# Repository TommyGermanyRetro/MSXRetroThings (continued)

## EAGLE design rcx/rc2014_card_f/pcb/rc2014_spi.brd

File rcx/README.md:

# RCX ROM cartridge - command reference

The RCX ROM cartridge manages up to 16 RC2014 cards. Its ROM (or the RAM driver `RCXRAM.COM`) adds BASIC `CALL` commands and an UNAPI/EXTBIOS interface; the SDCC library `rcx_io` bridges to the same functions. This page lists the general RCX commands; the commands of each card are on the card's page.

## Cards

+ [A) RC2014 card with PCF8584 I2C Controller (3 ports via Seeed) and PCF8583 battery buffered RTC](rc2014_card_a/README.md)
+ [B) RC2014 card SC103 with Z80 PIO](rc2014_card_b/README.md)
+ [C) RC2014 card with 8255A PIO](rc2014_card_c/README.md)
+ [D) RC2014 card with 8254A CTR](rc2014_card_d/README.md)
+ [E) RC2014 card with SJA1000 CAN controller (single use only)](rc2014_card_e/README.md)
+ [F) RC2014 card with 4x SPI bus up to 2 MHz via ATMEGA8](rc2014_card_f/README.md)
+ [G) RC2014 card with ADS1220 4 channel 24 bit A/D converter via ATMEGA8](rc2014_card_g/README.md)
+ [H) RC2014 card SC725 with Z80 SIO and Z80 CTC](rc2014_card_h/README.md)
+ [I) RC2014 card with MCP4822 4 channel 12 bit D/A converter via ATMEGA8](rc2014_card_i/README.md)

## Command reference

Commands implemented in ROM/DRV/LIB for steering and controlling of the cards functions:

+ <i><b>RCX ?</i></b>

  Prints the list of available RCX commands directly to the screen. Works independently from RCX INIT, so it is always safe to call even if no card has been registered yet.

|  | Definition | BASIC* | UNAPI | SDCC |
| --- | --- | --- | --- | --- |
| Syntax | RCX ? | _RCX ? | 1 | - (BASIC-only, not exposed) |

*) ROM only

+ <i><b>RCX INIT</i></b>

  Installs the RCX driver itself: allocates and clears the internal table that tracks which RC2014 card types are registered at which IO address. Every other RCX/card-specific command needs this table to exist, so it must run before any card-type INIT (I2C INIT, PIO INIT, etc.); calling it again while already installed just resets the table.

|  | Definition | BASIC* | UNAPI | SDCC |
| --- | --- | --- | --- | --- |
| Syntax | RCX INIT | _RCX INIT | 2 | Rcx_Init() |
| PARA 1 | Working area in RAM | automatic by BIOS | HL | word |

*) ROM only

+ <i><b>RCX ISINIT</i></b>

  Checks whether the RCX driver is already installed, without touching anything - same ISINIT/DEINIT/INIT pattern as XIO ISINIT.

|  | Definition | BASIC* | UNAPI | SDCC |
| --- | --- | --- | --- | --- |
| Syntax | RCX ISINIT | _RCX ISINIT() | 3 | Rcx_IsInit() |
| PARA 1 | 0 = not installed, 1 = installed | variable | DE as varptr | return value (byte) |

*) ROM only

+ <i><b>RCX DEINIT</i></b>

  Uninstalls the RCX driver and frees the card table again.

|  | Definition | BASIC* | UNAPI | SDCC |
| --- | --- | --- | --- | --- |
| Syntax | RCX DEINIT | _RCX DEINIT | 4 | Rcx_Deinit() |

*) ROM only

+ <i><b>RCX TABLE</i></b>

  Returns the RAM address of the internal per-slot card table directly, mainly useful for diagnostics - inspecting which addresses and card types are currently registered without a dedicated command for each one.

|  | Definition | BASIC* | UNAPI | SDCC |
| --- | --- | --- | --- | --- |
| Syntax | RCX TABLE | _RCX TABLE() | 5 | Rcx_GetTable() |
| PARA 1 | ADDR of RCX table | variable | DE as varptr | pointer (word) |

*) ROM only

## Folders

+ [rc2014_rom+ram/rom/](rc2014_rom+ram/rom/README.md) - ROM source and image
+ [rc2014_rom+ram/drv/](rc2014_rom+ram/drv/README.md) - RAM driver `RCXRAM.COM`
+ [rc2014_rom+ram/pcb/](rc2014_rom+ram/pcb/) - schematics and PCB of the ROM cartridge
+ [rc2014_adapter/pcb/](rc2014_adapter/pcb/) - schematics and PCB of the RC2014 adapter
+ [rcxslt/](rcxslt/) - RCX slot tools (BASIC, `.COM`, SDCC)

[↑ Main README](../README.md#2-msxretrothings---the-rcx-rom-cartridge-and-rc2014-cards)

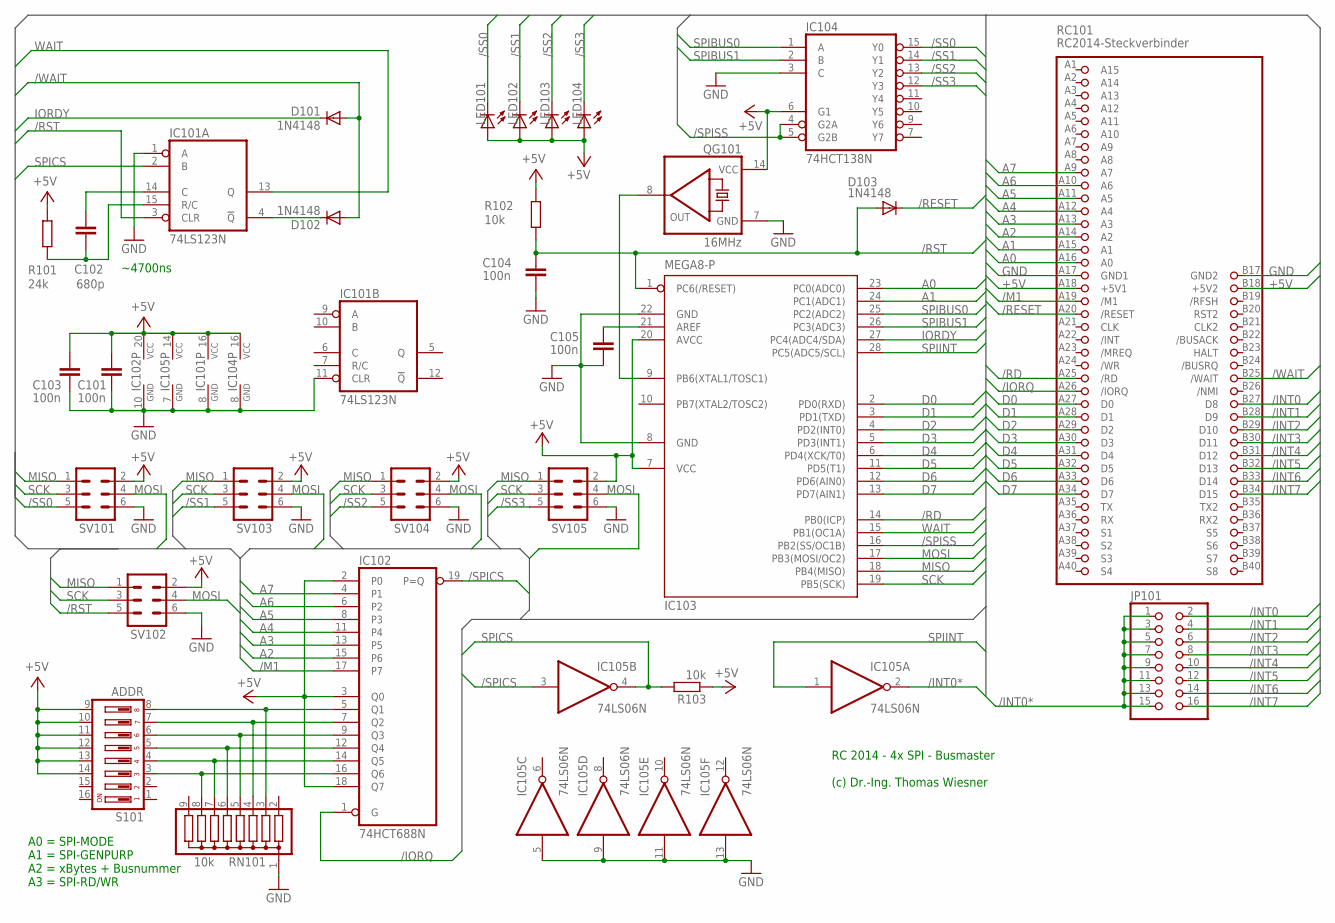
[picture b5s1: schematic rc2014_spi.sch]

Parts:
C101, C103, C104, C105: 100n; C025-025X050
C102: 680p; C025-025X050
D101, D102, D103: 1N4148; DO35-10
IC101: 74LS123N; DIL16
IC102: 74HCT688N; DIL20
IC103: MEGA8-P; DIL28-3
IC104: 74HCT138N; DIL16
IC105: 74LS06N; DIL14
JP101: PINHD-2X8; 2X08
LED101, LED102, LED103, LED104: LED3MM
QG101: 16MHz; DIL14S
R101: 24k; 0207/10
R102, R103: 10k; 0207/10
RC101: RC2014-Steckverbinder; RC2014-STECKER
RN101: 10k; SIL9
S101: ADDR; DS-08
SV101, SV102, SV103, SV104, SV105: ML6L

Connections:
+5V: C101.2, C103.2, IC101.16 (VCC), IC102.2 (P0), IC102.3 (Q0), IC102.18 (Q7), IC102.20 (VCC), IC103.7 (VCC), IC103.20 (AVCC), IC104.6 (G1), IC104.16 (VCC), IC105.14 (VCC), LED101.A, LED102.A, LED103.A, LED104.A, QG101.14 (VCC), R101.1, R102.1, R103.1, RC101.A18 (+5V1), RC101.B18 (+5V2), S101.9, S101.10, S101.11, S101.12, S101.13, S101.14, SV101.2, SV102.2, SV103.2, SV104.2, SV105.2
/INT0: JP101.2, RC101.B27 (D8)
/INT0*: IC105.2 (O), JP101.1, JP101.3, JP101.5, JP101.7, JP101.9, JP101.11, JP101.13, JP101.15
/INT1: JP101.4, RC101.B28 (D9)
/INT2: JP101.6, RC101.B29 (D10)
/INT3: JP101.8, RC101.B30 (D11)
/INT4: JP101.10, RC101.B31 (D12)
/INT5: JP101.12, RC101.B32 (D13)
/INT6: JP101.14, RC101.B33 (D14)
/INT7: JP101.16, RC101.B34 (D15)
/IORQ: IC102.1 (G), RC101.A26 (/IORQ)
/M1: IC102.17 (P7), RC101.A19 (/M1)
/RD: IC103.14 (PB0(ICP)), RC101.A25 (/RD)
/RESET: D103.C, RC101.A20 (/RESET)
/RST: C104.2, D103.A, IC101.3 (CLR), IC103.1 (PC6(/RESET)), R102.2, SV102.5
/SPICS: IC102.19 (P=Q), IC105.3 (I)
/SPISS: IC103.16 (PB2(SS/OC1B)), IC104.4 (G2A), IC104.5 (G2B)
/SS0: IC104.15 (Y0), LED101.K (C), SV101.5
/SS1: IC104.14 (Y1), LED102.K (C), SV103.5
/SS2: IC104.13 (Y2), LED103.K (C), SV104.5
/SS3: IC104.12 (Y3), LED104.K (C), SV105.5
/WAIT: D101.A, D102.A, RC101.B25 (/WAIT)
A0: IC103.23 (PC0(ADC0)), RC101.A16 (A0)
A1: IC103.24 (PC1(ADC1)), RC101.A15 (A1)
A2: IC102.15 (P6), RC101.A14 (A2)
A3: IC102.13 (P5), RC101.A13 (A3)
A4: IC102.11 (P4), RC101.A12 (A4)
A5: IC102.8 (P3), RC101.A11 (A5)
A6: IC102.6 (P2), RC101.A10 (A6)
A7: IC102.4 (P1), RC101.A9 (A7)
D0: IC103.2 (PD0(RXD)), RC101.A27 (D0)
D1: IC103.3 (PD1(TXD)), RC101.A28 (D1)
D2: IC103.4 (PD2(INT0)), RC101.A29 (D2)
D3: IC103.5 (PD3(INT1)), RC101.A30 (D3)
D4: IC103.6 (PD4(XCK/T0)), RC101.A31 (D4)
D5: IC103.11 (PD5(T1)), RC101.A32 (D5)
D6: IC103.12 (PD6(AIN0)), RC101.A33 (D6)
D7: IC103.13 (PD7(AIN1)), RC101.A34 (D7)
GND: C101.1, C103.1, C104.1, C105.1, IC101.1 (A), IC101.8 (GND), IC101.11 (CLR), IC102.10 (GND), IC103.8 (GND), IC103.22 (GND), IC104.3 (C), IC104.8 (GND), IC105.5 (I), IC105.7 (GND), IC105.9 (I), IC105.11 (I), IC105.13 (I), QG101.7 (GND), RC101.A17 (GND1), RC101.B17 (GND2), RN101.1, SV101.6, SV102.6, SV103.6, SV104.6, SV105.6
IORDY: D101.C, IC103.27 (PC4(ADC4/SDA))
MISO: IC103.18 (PB4(MISO)), SV101.1, SV102.1, SV103.1, SV104.1, SV105.1
MOSI: IC103.17 (PB3(MOSI/OC2)), SV101.4, SV102.4, SV103.4, SV104.4, SV105.4
unnamed: C102.1, IC101.15 (R/C), R101.2
unnamed: D102.C, IC101.4 (!Q)
unnamed: C105.2, IC103.21 (AREF)
unnamed: C102.2, IC101.14 (C)
unnamed: IC102.16 (Q6), RN101.8, S101.3
unnamed: IC102.14 (Q5), RN101.7, S101.4
unnamed: IC102.12 (Q4), RN101.6, S101.5
unnamed: IC102.9 (Q3), RN101.5, S101.6
unnamed: IC102.7 (Q2), RN101.4, S101.7
unnamed: IC102.5 (Q1), RN101.3, S101.8
QUARZ: IC103.9 (PB6(XTAL1/TOSC1)), QG101.8 (OUT)
SCK: IC103.19 (PB5(SCK)), SV101.3, SV102.3, SV103.3, SV104.3, SV105.3
SPIBUS0: IC103.25 (PC2(ADC2)), IC104.1 (A)
SPIBUS1: IC103.26 (PC3(ADC3)), IC104.2 (B)
SPICS: IC101.2 (B), IC105.4 (O), R103.2
SPIINT: IC103.28 (PC5(ADC5/SCL)), IC105.1 (I)
WAIT: IC101.13 (Q), IC103.15 (PB1(OC1A))

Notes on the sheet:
RC 2014 - 4x SPI - Busmaster (c) Dr.-Ing. Thomas Wiesner
~4700ns
A0 = SPI-MODE A1 = SPI-GENPURP A2 = xBytes + Busnummer A3 = SPI-RD/WR

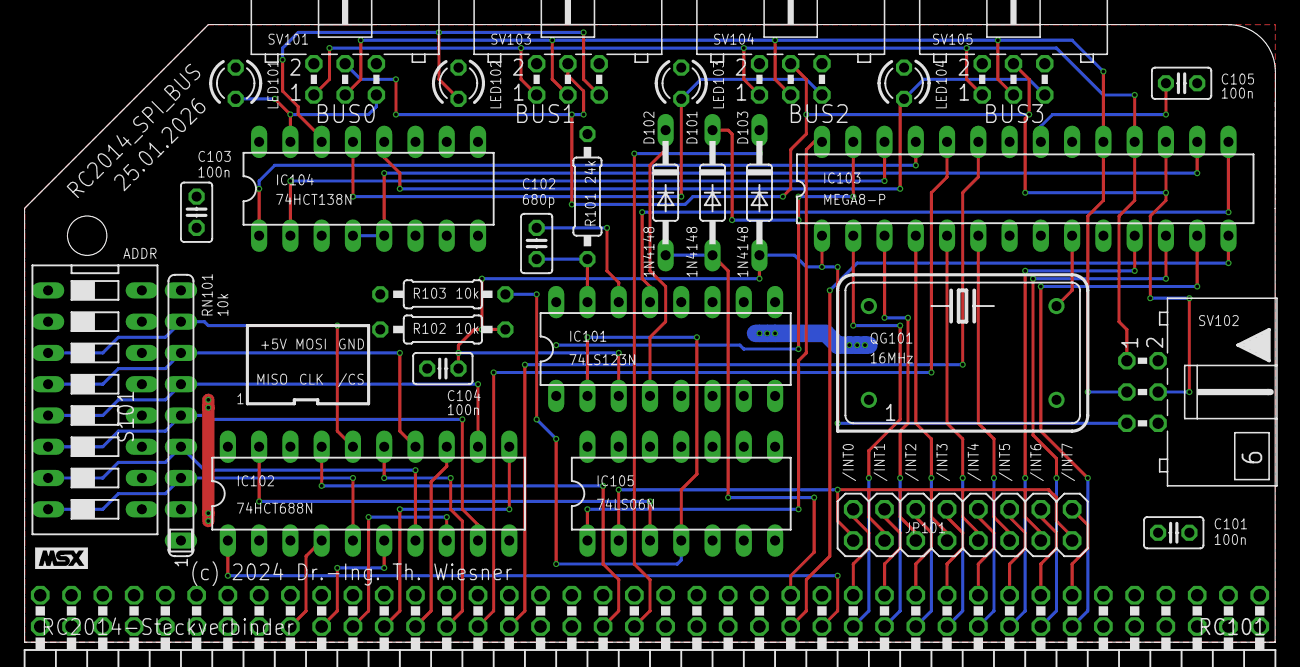
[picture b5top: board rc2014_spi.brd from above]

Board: 2 copper layers, 101.6 x 50.2 mm, 30 parts (0 on the bottom side), 59 nets.

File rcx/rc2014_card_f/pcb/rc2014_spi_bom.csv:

Qty,Reference,Value,Package,Description
1,RC101,RC2014,RC2014-STECKER,"RC2014 enhanced bus connector, pin header 2 x 40, 2.54 mm, angled"
1,IC103,ATmega8,DIL28-3,"Microcontroller ATmega8, flashed with atmel/MSXSPI/MSXSPI.ino"
1,IC102,74HCT688N,DIL20,8-bit comparator: card address against the DIP switch
1,IC104,74HCT138N,DIL16,3-to-8 decoder: SPI slave select /SS0-/SS3
1,IC101,74LS123N,DIL16,Dual monostable multivibrator
1,IC105,74LS06N,DIL14,"Hex inverter, open collector"
1,QG101,16MHz,DIL14S,"Crystal oscillator 16 MHz, DIL14 footprint"
4,"C101, C103, C104, C105",100n,C025-025X050,"Ceramic capacitor 100 nF, 2.5 mm pitch"
1,C102,680p,C025-025X050,"Ceramic capacitor 680 pF, 2.5 mm pitch"
3,"D101, D102, D103",1N4148,DO35-10,Signal diode
1,R101,24k,0207/10,"Resistor 24 kOhm, axial, 10 mm pitch"
2,"R102, R103",10k,0207/10,"Resistor 10 kOhm, axial, 10 mm pitch"
1,RN101,10k,SIL9,"Resistor network 8 x 10 kOhm, common pin, SIL9"
1,S101,ADDR,DS-08,DIP switch 8 positions: card address
4,"LED101, LED102, LED103, LED104",LED,LED3MM,LED 3 mm with built-in resistor for 5 V: SPI slave select /SS0-/SS3 active
4,"SV101, SV103, SV104, SV105",Box header 2x3,ML6L,"Box header 6 pins (2 x 3), 2.54 mm: SPI ports 0-3 (MISO, SCK, MOSI, /SS, +5 V, GND)"
1,SV102,Box header 2x3,ML6L,"Box header 6 pins (2 x 3), 2.54 mm: ISP connector of the ATmega8"
1,JP101,2X08,2X08,"Pin header 2 x 8, 2.54 mm, with jumper: selects the interrupt line /INT0-/INT7 of the XIO PIC"

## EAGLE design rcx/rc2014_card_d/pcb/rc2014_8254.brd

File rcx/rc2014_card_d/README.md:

# Card D - RC2014 card with 8254A CTR

RC2014 card with a 8254 CTR. Up to 16 cards are possible. The interrupt pins of TIMER 0 and 1 can be assigned to one of the XIO PIC interrupt channels. This module does not work with internal clock if 8253 (max. 1 MHz) is used.

## Command reference

Commands implemented in ROM:

+ <i><b>TIMER INIT</i></b>

  Registers the card's IO base address in the RCX table. Must be called once per card before any of the other TIMER commands below will find it.

|  | Definition | BASIC* | UNAPI | SDCC |
| --- | --- | --- | --- | --- |
| Syntax | TIMER INIT | _TIMER INIT() | 33 | Timer_Init() |
| PARA 1 | IO addr 0...251 | byte or variable | C | byte or variable |

*) ROM only

+ <i><b>TIMER 0 RD</i></b>

  Latches and reads the current 16-bit counter value of Timer 0.

|  | Definition | BASIC* | UNAPI | SDCC |
| --- | --- | --- | --- | --- |
| Syntax | TIMER 0 RD | _TIMER 0 RD() | 34 | Timer_Read0() |
| PARA 1 | IO addr 0...251 | byte or variable | C | byte or variable |
| PARA 2 | Word to read | variable | DE as varptr | return value (word) |
| PARA 3 | UNAPI ID Level 2 | -/- | B = 0 | - |

*) ROM only

+ <i><b>TIMER 0 WR</i></b>

  Loads a new 16-bit count/reload value into Timer 0.

|  | Definition | BASIC* | UNAPI | SDCC |
| --- | --- | --- | --- | --- |
| Syntax | TIMER 0 WR | _TIMER 0 WR() | 35 | Timer_Write0() |
| PARA 1 | IO addr 0...251 | byte or variable | C | byte or variable |
| PARA 2 | Word to write | word or variable | DE | word or variable |
| PARA 3 | UNAPI ID Level 2 | -/- | B = 1 | - |

*) ROM only

+ <i><b>TIMER 1 RD</i></b>

  Latches and reads the current 16-bit counter value of Timer 1.

|  | Definition | BASIC* | UNAPI | SDCC |
| --- | --- | --- | --- | --- |
| Syntax | TIMER 1 RD | _TIMER 1 RD() | 36 | Timer_Read1() |
| PARA 1 | IO addr 0...251 | byte or variable | C | byte or variable |
| PARA 2 | Word to read | variable | DE as varptr | return value (word) |
| PARA 3 | UNAPI ID Level 2 | -/- | B = 2 | - |

*) ROM only

+ <i><b>TIMER 1 WR</i></b>

  Loads a new 16-bit count/reload value into Timer 1.

|  | Definition | BASIC* | UNAPI | SDCC |
| --- | --- | --- | --- | --- |
| Syntax | TIMER 1 WR | _TIMER 1 WR() | 37 | Timer_Write1() |
| PARA 1 | IO addr 0...251 | byte or variable | C | byte or variable |
| PARA 2 | Word to write | word or variable | DE | word or variable |
| PARA 3 | UNAPI ID Level 2 | -/- | B = 3 | - |

*) ROM only

+ <i><b>TIMER 2 RD</i></b>

  Latches and reads the current 16-bit counter value of Timer 2.

|  | Definition | BASIC* | UNAPI | SDCC |
| --- | --- | --- | --- | --- |
| Syntax | TIMER 2 RD | _TIMER 2 RD() | 38 | Timer_Read2() |
| PARA 1 | IO addr 0...251 | byte or variable | C | byte or variable |
| PARA 2 | Word to read | variable | DE as varptr | return value (word) |
| PARA 3 | UNAPI ID Level 2 | -/- | B = 4 | - |

*) ROM only

+ <i><b>TIMER 2 WR</i></b>

  Loads a new 16-bit count/reload value into Timer 2.

|  | Definition | BASIC* | UNAPI | SDCC |
| --- | --- | --- | --- | --- |
| Syntax | TIMER 2 WR | _TIMER 2 WR() | 39 | Timer_Write2() |
| PARA 1 | IO addr 0...251 | byte or variable | C | byte or variable |
| PARA 2 | Word to write | word or variable | DE | word or variable |
| PARA 3 | UNAPI ID Level 2 | -/- | B = 5 | - |

*) ROM only

+ <i><b>TIMER CTRL</i></b>

  Writes the 82C54's mode-control word for one of the three counters - selects counting mode 0..5, BCD vs. binary counting and the read/write byte order, matching the 82C54 datasheet's control word format directly.

|  | Definition | BASIC* | UNAPI | SDCC |
| --- | --- | --- | --- | --- |
| Syntax | TIMER CTRL | _TIMER CTRL() | 40 | Timer_Ctrl() |
| PARA 1 | IO addr 0...251 | byte or variable | C | byte or variable |
| PARA 2 | Word to write | word or variable | E (D must be 0) | word or variable |
| PARA 3 | UNAPI ID Level 2 | -/- | B = 6 | - |

*) ROM only

+ <i><b>TIMER SET GATE</i></b>

  Drives one of the card's jumper-selectable GATE inputs high in software instead of wiring it permanently - only takes effect for a counter whose GATE jumper is actually set to the software-controlled position.

	Value 0..7 is allowed

|  | Definition | BASIC* | UNAPI | SDCC |
| --- | --- | --- | --- | --- |
| Syntax | TIMER SET GATE | _TIMER SET GATE() | 41 | Timer_SetGate() |
| PARA 1 | IO addr 0...251 | byte or variable | C | byte or variable |
| PARA 2 | GATE 0..3 (0..7) | byte or variable | E (D must be 0) | word or variable |
| PARA 3 | UNAPI ID Level 2 | -/- | B = 7 | - |

*) ROM only

+ <i><b>TIMER RESET GATE</i></b>

  Drives a jumper-selectable GATE input low again - the counterpart to TIMER SET GATE.

	Value 0..7 is allowed

|  | Definition | BASIC* | UNAPI | SDCC |
| --- | --- | --- | --- | --- |
| Syntax | TIMER RESET GATE | _TIMER RESET GATE() | 42 | Timer_ResetGate() |
| PARA 1 | IO addr 0...251 | byte or variable | C | byte or variable |
| PARA 2 | GATE 0..3 (0..7) | byte or variable | E (D must be 0) | word or variable |
| PARA 3 | UNAPI ID Level 2 | -/- | B = 8 | - |

*) ROM only

## Folders

+ [basic/](basic/README.md) - BASIC test programs
+ [com/](com/README.md) - `.COM` tools (UNAPI/EXTBIOS)
+ [sdcc/](sdcc/README.md) - SDCC tools
+ [pcb/](pcb/) - schematics, PCB, Gerber and drill files, bill of materials

[↑ Main README](../../README.md#d-rc2014-card-with-8254a-ctr)

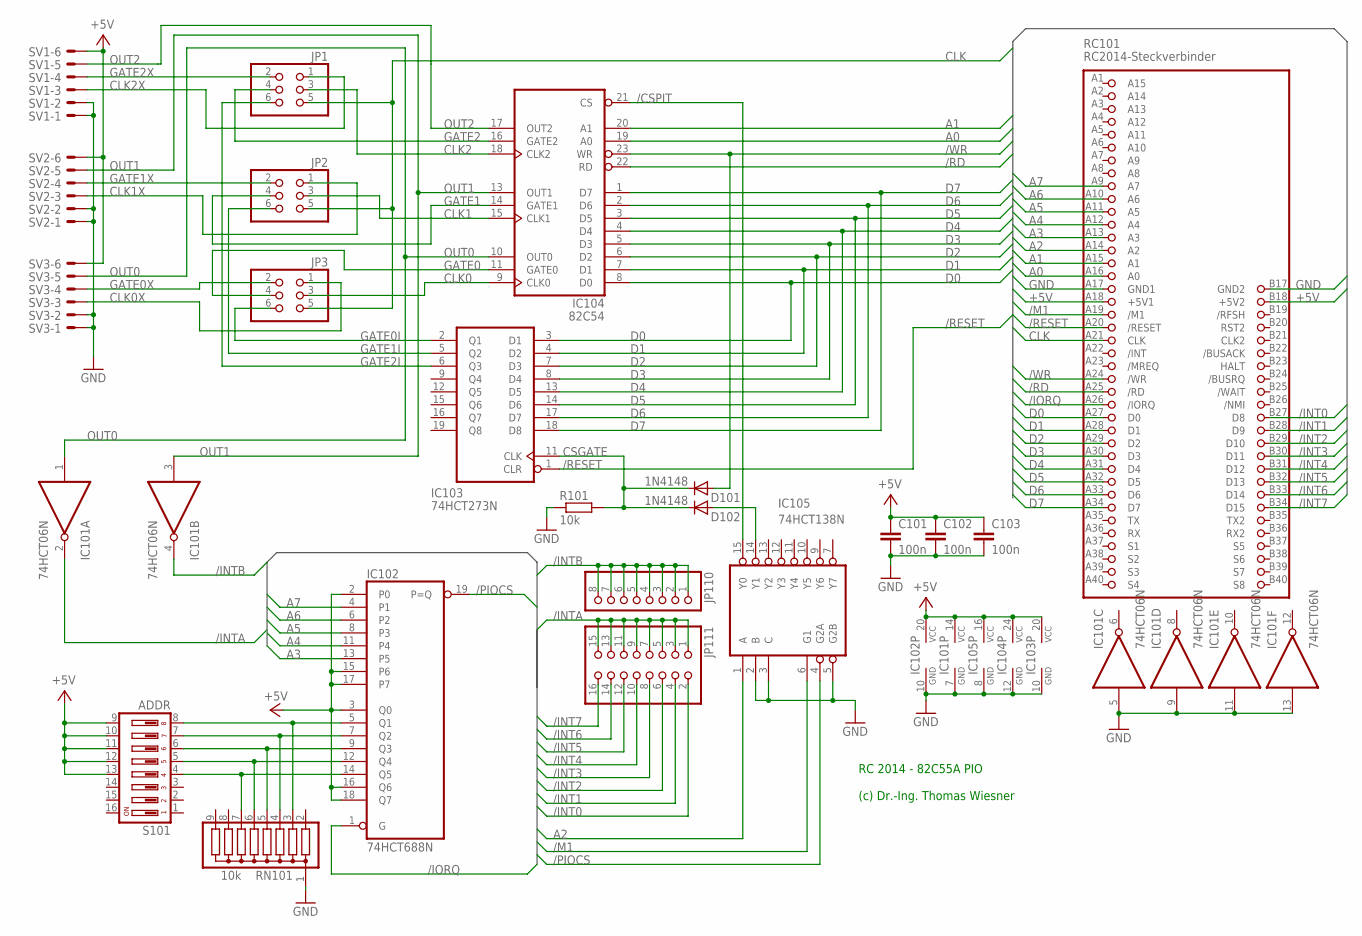
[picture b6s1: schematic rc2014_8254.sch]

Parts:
C101, C102, C103: 100n; C025-025X050
D101, D102: 1N4148; DO35-7
IC101: 74HCT06N; DIL14
IC102: 74HCT688N; DIL20
IC103: 74HCT273N; DIL20
IC104: 82C54; DIL24-6
IC105: 74HCT138N; DIL16
JP1, JP2, JP3: PINHD-2X3; 2X03
JP110: PINHD-1X8; 1X08
JP111: PINHD-2X8; 2X08
R101: 10k; 0207/10
RC101: RC2014-Steckverbinder; RC2014-STECKER
RN101: 10k; SIL9
S101: ADDR; DS-08
SV1, SV2, SV3: ML6LE; ML6L

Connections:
+5V: C101.1, C102.1, C103.1, IC101.14 (VCC), IC102.2 (P0), IC102.3 (Q0), IC102.15 (P6), IC102.16 (Q6), IC102.17 (P7), IC102.18 (Q7), IC102.20 (VCC), IC103.20 (VCC), IC104.24 (VCC), IC105.16 (VCC), RC101.A18 (+5V1), RC101.B18 (+5V2), S101.9, S101.10, S101.11, S101.12, S101.13, SV1.6, SV2.6, SV3.6
/CSPIT: IC104.21 (CS), IC105.15 (Y0)
/INT0: JP111.2, RC101.B27 (D8)
/INT1: JP111.4, RC101.B28 (D9)
/INT2: JP111.6, RC101.B29 (D10)
/INT3: JP111.8, RC101.B30 (D11)
/INT4: JP111.10, RC101.B31 (D12)
/INT5: JP111.12, RC101.B32 (D13)
/INT6: JP111.14, RC101.B33 (D14)
/INT7: JP111.16, RC101.B34 (D15)
/INTA: IC101.2 (O), JP111.1, JP111.3, JP111.5, JP111.7, JP111.9, JP111.11, JP111.13, JP111.15
/INTB: IC101.4 (O), JP110.1, JP110.2, JP110.3, JP110.4, JP110.5, JP110.6, JP110.7, JP110.8
/IORQ: IC102.1 (G), RC101.A26 (/IORQ)
/M1: IC105.6 (G1), RC101.A19 (/M1)
/PIOCS: IC102.19 (P=Q), IC105.4 (G2A)
/RD: IC104.22 (RD), RC101.A25 (/RD)
/RESET: IC103.1 (CLR), RC101.A20 (/RESET)
/WR: D101.A, IC104.23 (WR), RC101.A24 (/WR)
A0: IC104.19 (A0), RC101.A16 (A0)
A1: IC104.20 (A1), RC101.A15 (A1)
A2: IC105.1 (A), RC101.A14 (A2)
A3: IC102.13 (P5), RC101.A13 (A3)
A4: IC102.11 (P4), RC101.A12 (A4)
A5: IC102.8 (P3), RC101.A11 (A5)
A6: IC102.6 (P2), RC101.A10 (A6)
A7: IC102.4 (P1), RC101.A9 (A7)
CLK: JP1.5, JP2.5, JP3.5, RC101.A21 (CLK)
CLK0: IC104.9 (CLK0), JP3.3
CLK0X: JP3.1, SV3.3
CLK1: IC104.15 (CLK1), JP2.3
CLK1X: JP2.1, SV2.3
CLK2: IC104.18 (CLK2), JP1.3
CLK2X: JP1.1, SV1.3
CSGATE: D101.C, D102.C, IC103.11 (CLK), R101.2
D0: IC103.3 (D1), IC104.8 (D0), RC101.A27 (D0)
D1: IC103.4 (D2), IC104.7 (D1), RC101.A28 (D1)
D2: IC103.7 (D3), IC104.6 (D2), RC101.A29 (D2)
D3: IC103.8 (D4), IC104.5 (D3), RC101.A30 (D3)
D4: IC103.13 (D5), IC104.4 (D4), RC101.A31 (D4)
D5: IC103.14 (D6), IC104.3 (D5), RC101.A32 (D5)
D6: IC103.17 (D7), IC104.2 (D6), RC101.A33 (D6)
D7: IC103.18 (D8), IC104.1 (D7), RC101.A34 (D7)
GATE0: IC104.11 (GATE0), JP3.4
GATE0I: IC103.2 (Q1), JP3.6
GATE0X: JP3.2, SV3.4
GATE1: IC104.14 (GATE1), JP2.4
GATE1I: IC103.5 (Q2), JP2.6
GATE1X: JP2.2, SV2.4
GATE2: IC104.16 (GATE2), JP1.4
GATE2I: IC103.6 (Q3), JP1.6
GATE2X: JP1.2, SV1.4
GND: C101.2, C102.2, C103.2, IC101.5 (I), IC101.7 (GND), IC101.9 (I), IC101.11 (I), IC101.13 (I), IC102.10 (GND), IC103.10 (GND), IC104.12 (GND), IC105.2 (B), IC105.3 (C), IC105.5 (G2B), IC105.8 (GND), R101.1, RC101.A17 (GND1), RC101.B17 (GND2), RN101.1, SV1.1, SV1.2, SV2.1, SV2.2, SV3.1, SV3.2
unnamed: D102.A, IC105.14 (Y1)
unnamed: IC102.14 (Q5), RN101.7, S101.4
unnamed: IC102.12 (Q4), RN101.6, S101.5
unnamed: IC102.9 (Q3), RN101.5, S101.6
unnamed: IC102.7 (Q2), RN101.4, S101.7
unnamed: IC102.5 (Q1), RN101.3, S101.8
OUT0: IC101.1 (I), IC104.10 (OUT0), SV3.5
OUT1: IC101.3 (I), IC104.13 (OUT1), SV2.5
OUT2: IC104.17 (OUT2), SV1.5

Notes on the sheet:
RC 2014 - 82C55A PIO (c) Dr.-Ing. Thomas Wiesner

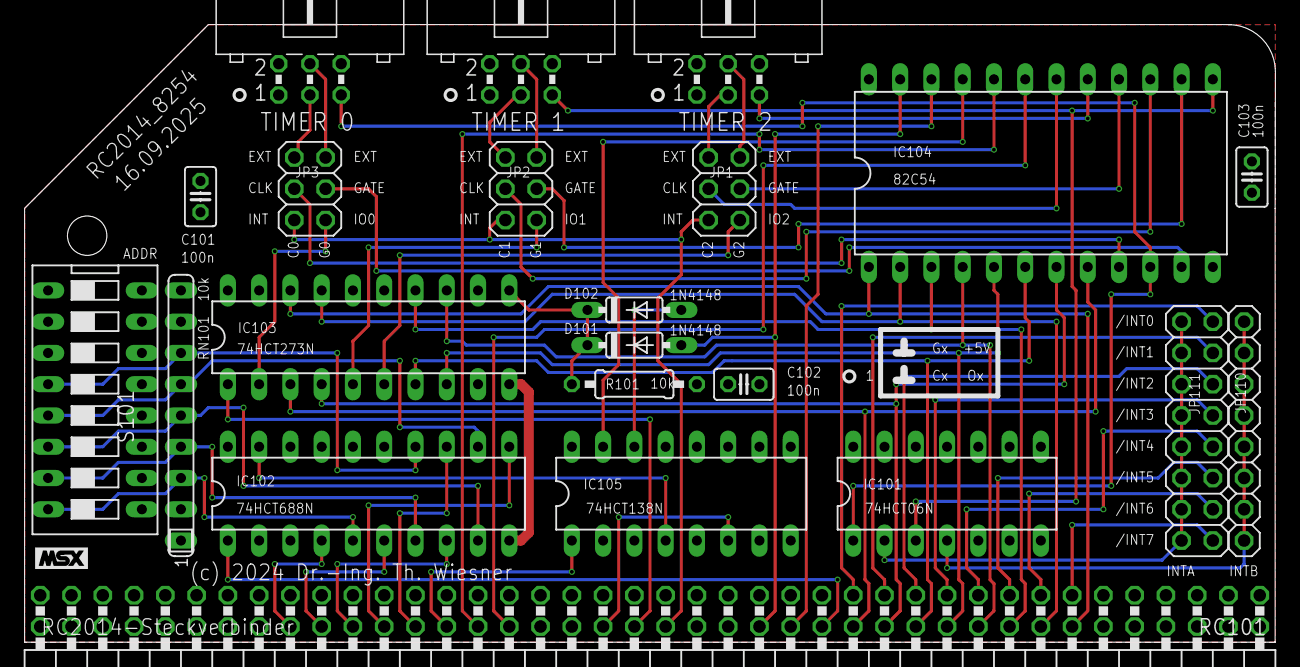
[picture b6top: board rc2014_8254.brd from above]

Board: 2 copper layers, 101.6 x 50.2 mm, 22 parts (0 on the bottom side), 61 nets.

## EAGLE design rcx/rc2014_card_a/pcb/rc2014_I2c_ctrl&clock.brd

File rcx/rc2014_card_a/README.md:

# Card A - RC2014 card with PCF8584 I2C Controller (3 ports via Seeed) and PCF8583 battery buffered RTC

This RC2014 card contains an I2C bus controller PCF8584 and a PCF8583 RTC buffered by battery. The interrupt pins of both chips can be assigned to one of the XIO PIC interrupt channels.

## Command reference

Commands implemented in ROM:

+ <i><b>I2C INIT</i></b>

  Registers the card's IO base address in the RCX table. Must be called once per card before any of the other I2C/RTC commands below will find it.

|  | Definition | BASIC* | UNAPI | SDCC |
| --- | --- | --- | --- | --- |
| Syntax | I2C INIT | _I2C INIT() | 6 | I2c_Init() |
| PARA 1 | IO addr 0...254 | byte or variable | C | byte or variable |

*) ROM only

+ <i><b>I2C WR</i></b>

  Writes a single byte to a specific I2C slave device's address on the bus - the basic building block for talking to anything hanging off the PCF8584 (an LCD, a sensor, another RTC, ...).

|  | Definition | BASIC* | UNAPI | SDCC |
| --- | --- | --- | --- | --- |
| Syntax | I2C WR | _I2C WR() | 7 | I2c_Write() |
| PARA 1 | IO bus addr 0...254 | byte or variable | E | byte or variable |
| PARA 2 | I2C addr 0...254 | byte or variable | C | byte or variable |
| PARA 3 | Data | byte or variable | B | byte or variable |

*) ROM only

+ <i><b>I2C WRB</i></b>

  Writes an arbitrary-length block of bytes to a specific I2C slave in one call, instead of looping single I2C WR calls - used e.g. to send a whole HD44780 LCD command/data sequence at once.

|  | Definition | BASIC* | UNAPI | SDCC |
| --- | --- | --- | --- | --- |
| Syntax | I2C WRB | _I2C WRB() | 8 | I2c_Wrb() |
| PARA 1 | IO bus addr 0...254 | byte or variable | H | byte or variable |
| PARA 2 | I2C addr 0...254 | byte or variable | C | byte or variable |
| PARA 3 | Length | byte or variable | B | byte or variable |
| PARA 4 | Data | array index 0 | DE as varptr | pointer |

*) ROM only

+ <i><b>I2C RD</i></b>

  Reads a single byte back from a specific I2C slave device's address.

|  | Definition | BASIC* | UNAPI | SDCC |
| --- | --- | --- | --- | --- |
| Syntax | I2C RD | _I2C RD() | 9 | I2c_Read() |
| PARA 1 | IO bus addr 0...254 | byte or variable | C | byte or variable |
| PARA 2 | I2C addr 0...254 | byte or variable | B | byte or variable |
| PARA 3 | Data | variable | DE as varptr | return value (byte) |

*) ROM only

+ <i><b>I2C RDB</i></b>

  Reads an arbitrary-length block of bytes back from a specific I2C slave in one call.

|  | Definition | BASIC* | UNAPI | SDCC |
| --- | --- | --- | --- | --- |
| Syntax | I2C RDB | _I2C RDB() | 10 | I2c_Rdb() |
| PARA 1 | IO bus addr 0...254 | byte or variable | H | byte or variable |
| PARA 2 | I2C addr 0...254 | byte or variable | C | byte or variable |
| PARA 3 | Length | byte or variable | B | byte or variable |
| PARA 4 | Data | array index 0 | DE as varptr | pointer |

*) ROM only

+ <i><b>I2C RESET</i></b>

  Resets the PCF8584 I2C bus controller itself (not a specific slave device) - useful to recover a bus that got stuck, e.g. after a slave was interrupted mid-transfer.

|  | Definition | BASIC* | UNAPI | SDCC |
| --- | --- | --- | --- | --- |
| Syntax | I2C RESET | _I2C RESET() | 11 | I2c_Reset() |
| PARA 1 | IO addr 0...254 | byte or variable | C | byte or variable |

*) ROM only

+ <i><b>SET TIME</i></b>

  Writes the time-of-day into the on-board PCF8583 RTC, as an 8-character `HH:MM:SS` string.

|  | Definition | BASIC* | UNAPI | SDCC |
| --- | --- | --- | --- | --- |
| Syntax | SET TIME | _SET TIME RD() | 12 | Rtc_SetTime() |
| PARA 1 | IO bus addr 0...254 | byte or variable | C | byte or variable |
| PARA 2 | TIME | String variable len = 8 | DE as varptr | pointer (8 bytes) |

*) ROM only

+ <i><b>GET TIME</i></b>

  Reads the current time-of-day back from the PCF8583 RTC, as an 8-character `HH:MM:SS` string.

|  | Definition | BASIC* | UNAPI | SDCC |
| --- | --- | --- | --- | --- |
| Syntax | GET TIME | _GET TIME RD() | 13 | Rtc_GetTime() |
| PARA 1 | IO bus addr 0...254 | byte or variable | C | byte or variable |
| PARA 2 | TIME | String variable len = 8 | DE as varptr | pointer (8 bytes) |

*) ROM only

+ <i><b>SET DATE</i></b>

  Writes the date into the on-board PCF8583 RTC, as an 8-character `DD/MM/YY` string.

|  | Definition | BASIC* | UNAPI | SDCC |
| --- | --- | --- | --- | --- |
| Syntax | SET DATE | _SET DATE RD() | 14 | Rtc_SetDate() |
| PARA 1 | IO bus addr 0...254 | byte or variable | C | byte or variable |
| PARA 2 | DATE | String variable len = 8 | DE as varptr | pointer (8 bytes) |

*) ROM only

+ <i><b>GET DATE</i></b>

  Reads the current date back from the PCF8583 RTC, as an 8-character `DD/MM/YY` string.

|  | Definition | BASIC* | UNAPI | SDCC |
| --- | --- | --- | --- | --- |
| Syntax | GET DATE | _GET DATE RD() | 15 | Rtc_GetDate() |
| PARA 1 | IO bus addr 0...254 | byte or variable | C | byte or variable |
| PARA 2 | DATE | String variable len = 8 | DE as varptr | pointer (8 bytes) |

*) ROM only

## Folders

+ [basic/](basic/README.md) - BASIC test programs
+ [com/](com/README.md) - `.COM` tools (UNAPI/EXTBIOS)
+ [sdcc/](sdcc/README.md) - SDCC tools
+ [tsr/](tsr/README.md) - MemMan TSR
+ [pcb/](pcb/) - schematics, PCB, Gerber and drill files, bill of materials

[↑ Main README](../../README.md#a-rc2014-card-with-pcf8584-i2c-controller-3-ports-via-seeed-and-pcf8583-battery-buffered-rtc)

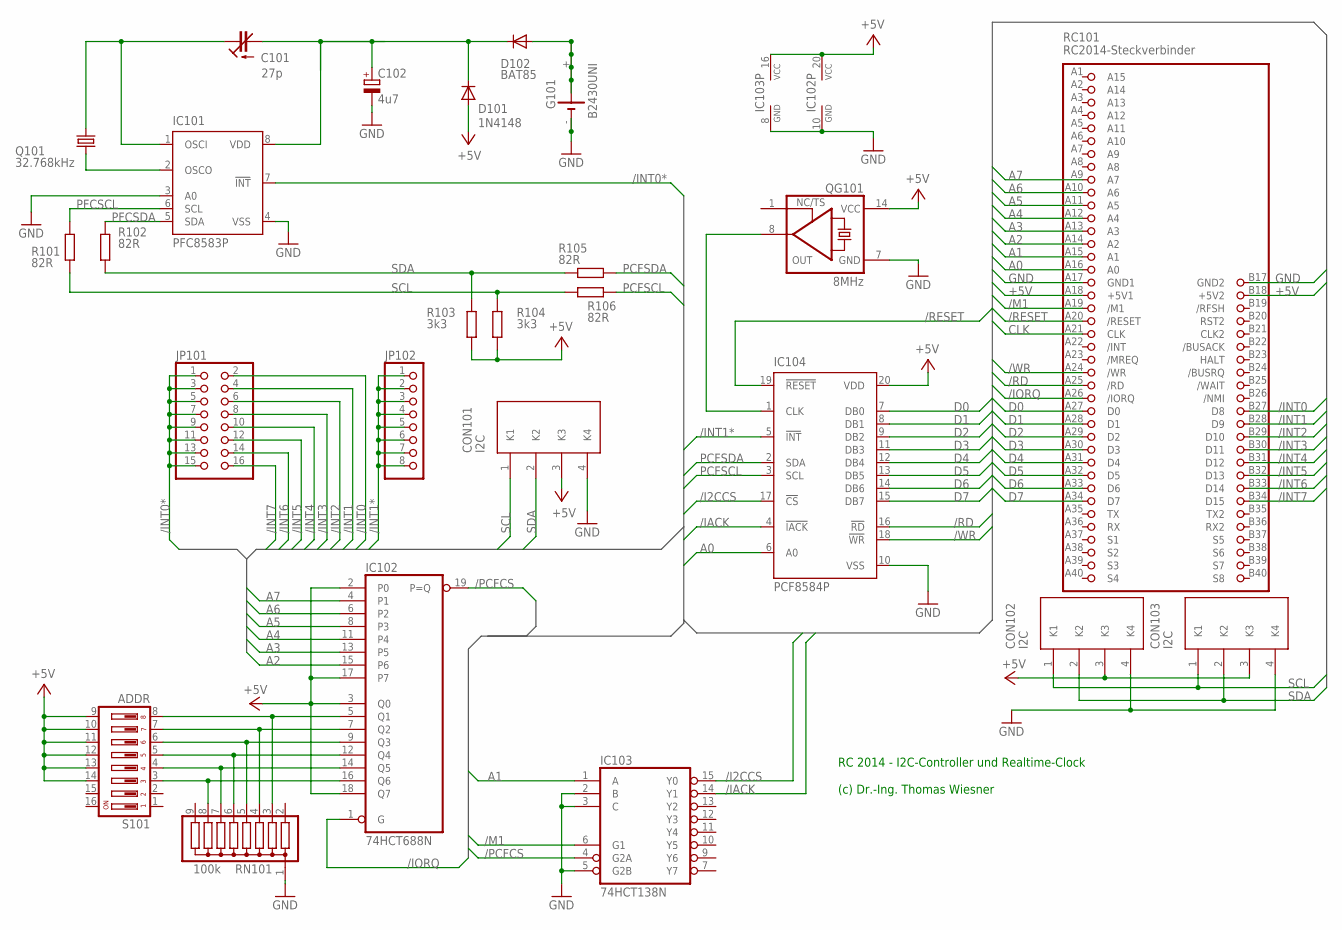
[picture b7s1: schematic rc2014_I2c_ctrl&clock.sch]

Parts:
C101: 27p; CTRIM3050.504
C102: 4u7; E2,5-6
CON101, CON102, CON103: I2C; JST-04-ST90
D101: 1N4148; DO35-7
D102: BAT85; DO34-7
G101: B2430UNI
IC101: PFC8583P; DIL08
IC102: 74HCT688N; DIL20
IC103: 74HCT138N; DIL16
IC104: PCF8584P; DIL20
JP101: PINHD-2X8; 2X08
JP102: PINHD-1X8; 1X08
Q101: 32.768kHz; TC26H
QG101: 8MHz; DIL14S
R101, R102, R105, R106: 82R; 0207/10
R103, R104: 3k3; 0207/10
RC101: RC2014-Steckverbinder; RC2014-STECKER
RN101: 100k; SIL9
S101: ADDR; DS-08

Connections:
+5V: CON101.3 (K3), CON102.3 (K3), CON103.3 (K3), D101.A, IC102.2 (P0), IC102.3 (Q0), IC102.17 (P7), IC102.18 (Q7), IC102.20 (VCC), IC103.16 (VCC), IC104.20 (VDD), QG101.14 (VCC), R103.1, R104.1, RC101.A18 (+5V1), RC101.B18 (+5V2), S101.9, S101.10, S101.11, S101.12, S101.13, S101.14
/I2CCS: IC103.15 (Y0), IC104.17 (!CS)
/IACK: IC103.14 (Y1), IC104.4 (!IACK)
/INT0: JP101.2, RC101.B27 (D8)
/INT0*: IC101.7 (!INT), JP101.1, JP101.3, JP101.5, JP101.7, JP101.9, JP101.11, JP101.13, JP101.15
/INT1: JP101.4, RC101.B28 (D9)
/INT1*: IC104.5 (!INT), JP102.1, JP102.2, JP102.3, JP102.4, JP102.5, JP102.6, JP102.7, JP102.8
/INT2: JP101.6, RC101.B29 (D10)
/INT3: JP101.8, RC101.B30 (D11)
/INT4: JP101.10, RC101.B31 (D12)
/INT5: JP101.12, RC101.B32 (D13)
/INT6: JP101.14, RC101.B33 (D14)
/INT7: JP101.16, RC101.B34 (D15)
/IORQ: IC102.1 (G), RC101.A26 (/IORQ)
/M1: IC103.6 (G1), RC101.A19 (/M1)
/PCFCS: IC102.19 (P=Q), IC103.4 (G2A)
/RD: IC104.16 (!RD), RC101.A25 (/RD)
/RESET: IC104.19 (!RESET), RC101.A20 (/RESET)
/WR: IC104.18 (!WR), RC101.A24 (/WR)
A0: IC104.6 (A0), RC101.A16 (A0)
A1: IC103.1 (A), RC101.A15 (A1)
A2: IC102.15 (P6), RC101.A14 (A2)
A3: IC102.13 (P5), RC101.A13 (A3)
A4: IC102.11 (P4), RC101.A12 (A4)
A5: IC102.8 (P3), RC101.A11 (A5)
A6: IC102.6 (P2), RC101.A10 (A6)
A7: IC102.4 (P1), RC101.A9 (A7)
CLK: RC101.A21 (CLK)
D0: IC104.7 (DB0), RC101.A27 (D0)
D1: IC104.8 (DB1), RC101.A28 (D1)
D2: IC104.9 (DB2), RC101.A29 (D2)
D3: IC104.11 (DB3), RC101.A30 (D3)
D4: IC104.12 (DB4), RC101.A31 (D4)
D5: IC104.13 (DB5), RC101.A32 (D5)
D6: IC104.14 (DB6), RC101.A33 (D6)
D7: IC104.15 (DB7), RC101.A34 (D7)
GND: C102.-, CON101.4 (K4), CON102.4 (K4), CON103.4 (K4), G101.-, G101.-@1 (-), IC101.3 (A0), IC101.4 (VSS), IC102.10 (GND), IC103.2 (B), IC103.3 (C), IC103.5 (G2B), IC103.8 (GND), IC104.10 (VSS), QG101.7 (GND), RC101.A17 (GND1), RC101.B17 (GND2), RN101.1
unnamed: IC104.1 (CLK), QG101.8 (OUT)
unnamed: IC101.2 (OSCO), Q101.1
unnamed: D102.A, G101.+, G101.+@1 (+), G101.+@2 (+), G101.+@3 (+), G101.+@4 (+)
unnamed: IC102.16 (Q6), RN101.8, S101.3
unnamed: IC102.14 (Q5), RN101.7, S101.4
unnamed: IC102.12 (Q4), RN101.6, S101.5
unnamed: IC102.9 (Q3), RN101.5, S101.6
unnamed: IC102.7 (Q2), RN101.4, S101.7
unnamed: IC102.5 (Q1), RN101.3, S101.8
unnamed: C101.1 (E), IC101.1 (OSCI), Q101.2
PCFSCL: IC104.3 (SCL), R106.2
PCFSDA: IC104.2 (SDA), R105.2
PFCSCL: IC101.6 (SCL), R101.1
PFCSDA: IC101.5 (SDA), R102.1
SCL: CON101.1 (K1), CON102.1 (K1), CON103.1 (K1), R101.2, R104.2, R106.1
SDA: CON101.2 (K2), CON102.2 (K2), CON103.2 (K2), R102.2, R103.2, R105.1
UBATT: C101.2 (A), C102.+, D101.C, D102.C, IC101.8 (VDD)

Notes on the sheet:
RC 2014 - I2C-Controller und Realtime-Clock (c) Dr.-Ing. Thomas Wiesner

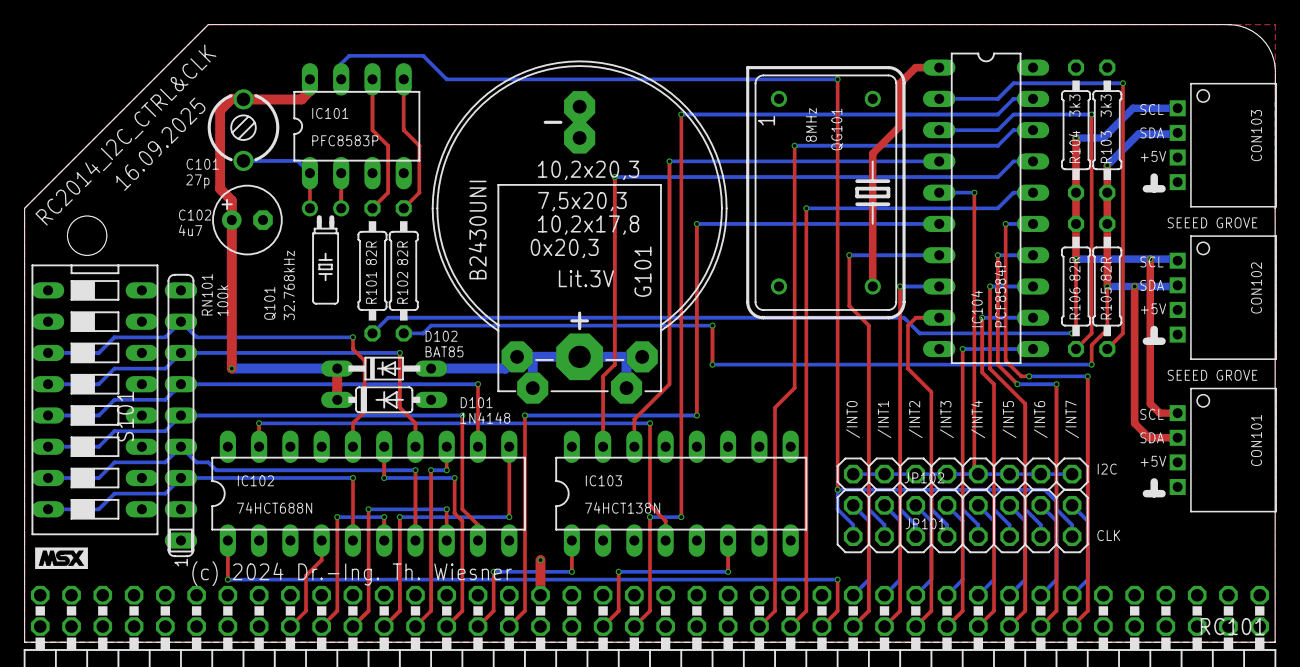
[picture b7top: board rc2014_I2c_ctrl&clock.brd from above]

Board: 2 copper layers, 101.6 x 50.2 mm, 25 parts (0 on the bottom side), 53 nets.

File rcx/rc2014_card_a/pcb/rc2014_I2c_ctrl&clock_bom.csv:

Qty,Reference,Value,Package,Description
1,RC101,RC2014,RC2014-STECKER,"RC2014 enhanced bus connector, pin header 2 x 40, 2.54 mm, angled"
1,IC104,PCF8584P,DIL20,I2C bus controller (NXP PCF8584)
1,IC101,PCF8583P,DIL08,"Clock/calendar with 240 bytes RAM, I2C (NXP PCF8583)"
1,IC102,74HCT688N,DIL20,8-bit comparator: card address against the DIP switch
1,IC103,74HCT138N,DIL16,3-to-8 decoder
1,QG101,8MHz,DIL14S,"Crystal oscillator 8 MHz, DIL14 footprint"
1,Q101,32.768kHz,TC26H,"Watch crystal 32.768 kHz, cylindrical 2 x 6 mm"
1,C101,27p,CTRIM3050.504,Trimmer capacitor about 27 pF: clock adjustment
1,C102,4u7,"E2,5-6","Electrolytic capacitor 4.7 uF, radial, 2.5 mm pitch"
1,G101,B2430UNI,B2430UNI,Holder for coin cell CR2430: battery backup of the clock
1,D101,1N4148,DO35-7,Signal diode
1,D102,BAT85,DO34-7,Schottky diode
4,"R101, R102, R105, R106",82R,0207/10,"Resistor 82 Ohm, axial, 10 mm pitch"
2,"R103, R104",3k3,0207/10,"Resistor 3k3, axial, 10 mm pitch: I2C pull-ups"
1,RN101,100k,SIL9,"Resistor network 8 x 100 kOhm, common pin, SIL9"
1,S101,ADDR,DS-08,DIP switch 8 positions: card address
3,"CON101, CON102, CON103",I2C,JST-04-ST90,"I2C socket 4 pins (SCL, SDA, +5 V, GND), JST, angled"
1,JP101,2X08,2X08,"Pin header 2 x 8, 2.54 mm, with jumper: selects the interrupt line /INT0-/INT7 of the XIO PIC"
1,JP102,1X08,1X08,"Pin header 1 x 8, 2.54 mm: second interrupt source /INT1*"

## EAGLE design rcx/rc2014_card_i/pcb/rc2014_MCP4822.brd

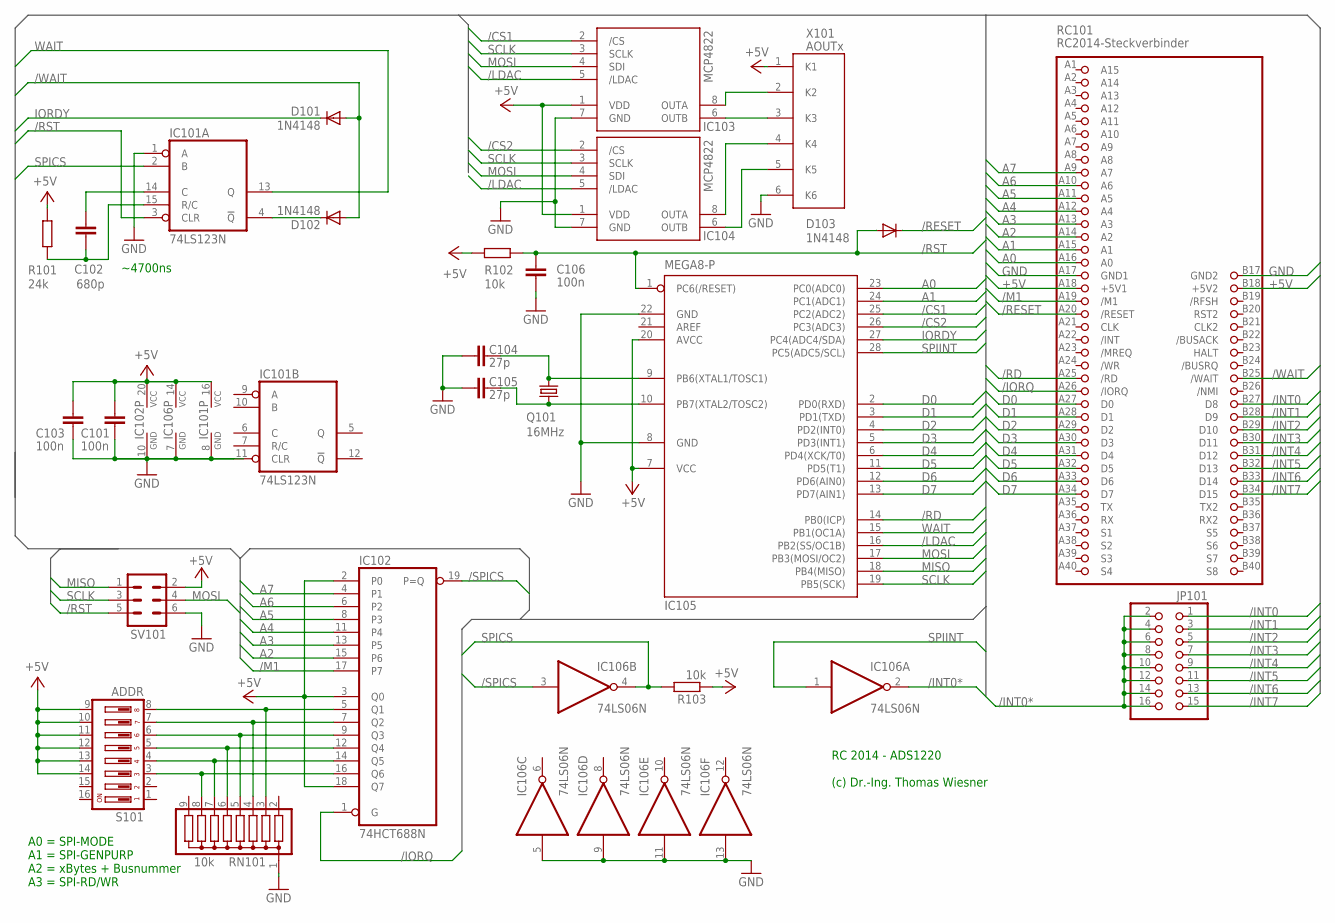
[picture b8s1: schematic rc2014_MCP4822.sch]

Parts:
C101, C103, C106: 100n; C025-025X050
C102: 680p; C025-025X050
C104, C105: 27p; C025-025X050
D101, D102, D103: 1N4148; DO35-10
IC101: 74LS123N; DIL16
IC102: 74HCT688N; DIL20
IC103, IC104: MCP4822; DIL08
IC105: MEGA8-P; DIL28-3
IC106: 74LS06N; DIL14
JP101: PINHD-2X8; 2X08
Q101: 16MHz; HC49U-V
R101: 24k; 0207/10
R102, R103: 10k; 0207/10
RC101: RC2014-Steckverbinder; RC2014-STECKER
RN101: 10k; SIL9
S101: ADDR; DS-08
SV101: ML6L
X101: AOUTx; AKL182-6

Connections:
+5V: C101.2, C103.2, IC101.16 (VCC), IC102.2 (P0), IC102.3 (Q0), IC102.18 (Q7), IC102.20 (VCC), IC103.1 (VDD), IC104.1 (VDD), IC105.7 (VCC), IC105.20 (AVCC), IC106.14 (VCC), R101.1, R102.1, R103.1, RC101.A18 (+5V1), RC101.B18 (+5V2), S101.9, S101.10, S101.11, S101.12, S101.13, S101.14, SV101.2, X101.1 (K1)
/CS1: IC103.2 (/CS), IC105.25 (PC2(ADC2))
/CS2: IC104.2 (/CS), IC105.26 (PC3(ADC3))
/INT0: JP101.1, RC101.B27 (D8)
/INT0*: IC106.2 (O), JP101.2, JP101.4, JP101.6, JP101.8, JP101.10, JP101.12, JP101.14, JP101.16
/INT1: JP101.3, RC101.B28 (D9)
/INT2: JP101.5, RC101.B29 (D10)
/INT3: JP101.7, RC101.B30 (D11)
/INT4: JP101.9, RC101.B31 (D12)
/INT5: JP101.11, RC101.B32 (D13)
/INT6: JP101.13, RC101.B33 (D14)
/INT7: JP101.15, RC101.B34 (D15)
/IORQ: IC102.1 (G), RC101.A26 (/IORQ)
/LDAC: IC103.5 (/LDAC), IC104.5 (/LDAC), IC105.16 (PB2(SS/OC1B))
/M1: IC102.17 (P7), RC101.A19 (/M1)
/RD: IC105.14 (PB0(ICP)), RC101.A25 (/RD)
/RESET: D103.C, RC101.A20 (/RESET)
/RST: C106.2, D103.A, IC101.3 (CLR), IC105.1 (PC6(/RESET)), R102.2, SV101.5
/SPICS: IC102.19 (P=Q), IC106.3 (I)
/WAIT: D101.A, D102.A, RC101.B25 (/WAIT)
A0: IC105.23 (PC0(ADC0)), RC101.A16 (A0)
A1: IC105.24 (PC1(ADC1)), RC101.A15 (A1)
A2: IC102.15 (P6), RC101.A14 (A2)
A3: IC102.13 (P5), RC101.A13 (A3)
A4: IC102.11 (P4), RC101.A12 (A4)
A5: IC102.8 (P3), RC101.A11 (A5)
A6: IC102.6 (P2), RC101.A10 (A6)
A7: IC102.4 (P1), RC101.A9 (A7)
D0: IC105.2 (PD0(RXD)), RC101.A27 (D0)
D1: IC105.3 (PD1(TXD)), RC101.A28 (D1)
D2: IC105.4 (PD2(INT0)), RC101.A29 (D2)
D3: IC105.5 (PD3(INT1)), RC101.A30 (D3)
D4: IC105.6 (PD4(XCK/T0)), RC101.A31 (D4)
D5: IC105.11 (PD5(T1)), RC101.A32 (D5)
D6: IC105.12 (PD6(AIN0)), RC101.A33 (D6)
D7: IC105.13 (PD7(AIN1)), RC101.A34 (D7)
GND: C101.1, C103.1, C104.2, C105.2, C106.1, IC101.1 (A), IC101.8 (GND), IC101.11 (CLR), IC102.10 (GND), IC103.7 (GND), IC104.7 (GND), IC105.8 (GND), IC105.22 (GND), IC106.5 (I), IC106.7 (GND), IC106.9 (I), IC106.11 (I), IC106.13 (I), RC101.A17 (GND1), RC101.B17 (GND2), RN101.1, SV101.6, X101.6 (K6)
IORDY: D101.C, IC105.27 (PC4(ADC4/SDA))
MISO: IC105.18 (PB4(MISO)), SV101.1
MOSI: IC103.4 (SDI), IC104.4 (SDI), IC105.17 (PB3(MOSI/OC2)), SV101.4
unnamed: C102.1, IC101.15 (R/C), R101.2
unnamed: D102.C, IC101.4 (!Q)
unnamed: C105.1, IC105.10 (PB7(XTAL2/TOSC2)), Q101.1
unnamed: C102.2, IC101.14 (C)
unnamed: C104.1, IC105.9 (PB6(XTAL1/TOSC1)), Q101.2
unnamed: IC102.16 (Q6), RN101.8, S101.3
unnamed: IC102.14 (Q5), RN101.7, S101.4
unnamed: IC102.12 (Q4), RN101.6, S101.5
unnamed: IC102.9 (Q3), RN101.5, S101.6
unnamed: IC102.7 (Q2), RN101.4, S101.7
unnamed: IC102.5 (Q1), RN101.3, S101.8
unnamed: IC103.8 (OUTA), X101.2 (K2)
unnamed: IC103.6 (OUTB), X101.3 (K3)
unnamed: IC104.8 (OUTA), X101.4 (K4)
unnamed: IC104.6 (OUTB), X101.5 (K5)
SCLK: IC103.3 (SCLK), IC104.3 (SCLK), IC105.19 (PB5(SCK)), SV101.3
SPICS: IC101.2 (B), IC106.4 (O), R103.2
SPIINT: IC105.28 (PC5(ADC5/SCL)), IC106.1 (I)
WAIT: IC101.13 (Q), IC105.15 (PB1(OC1A))

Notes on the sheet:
RC 2014 - ADS1220 (c) Dr.-Ing. Thomas Wiesner
~4700ns
A0 = SPI-MODE A1 = SPI-GENPURP A2 = xBytes + Busnummer A3 = SPI-RD/WR
